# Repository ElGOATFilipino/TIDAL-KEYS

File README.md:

# TIDAL-KEYS

A 48 button BLE split keyboard with a design based on the geometry dash level "Tidal wave", features 20 SK6803MINI-E Leds total, and uses ZMK firmware. It is meant to be used as a regular keyboard, and the distance between each half is up to the user.

I made this because I wanted a split keyboard that felt unique to me! And since I love the game "geometry dash", I decided to base the design around one of its most popular community levels: Tidal wave. 

## Features per side:
- 24 white DSA keys
- 10 neopixel SK6803MINI-E LEDs (Light blue glow under the keys)
- BLE
- Hotswap keys
- 1000mAh 1S LiPo battery per side
- Battery sensing

## CAD Model: 

Both cases (left and right) are held together using 10 M2 screws and 10 heatset inserts per side. On both halves, 6 screws are used for the pcb and 4 of them for the top part of the case.
The case is made of only three separate pieces: the bottom, the top cover and the battery lid.

**Features of each component:**
- Bottom case: The bottom case has a hole, meant for the battery. This section also has a "tunnel" where the battery cables can easily connect to the PCB battery pads.
- Top lid: The top part features different types decorations from the level "Tidal wave", such as starfish, bubbles and its iconic title screen arrows.
- Battery lid: The battery lid is screwed to the case using 2 self-tapping M2 screws. The PCB sits over the bottom case using a 3x5x3mm spacer at the bottom and a 3x5x2mm spacer at the top per screw; sandwiching the PCB between them to prevent vertical wobble.

All case components made using Fusion 360.

## PCB:

Both the schematic and the PCB were designed in Kicad!

**Schematic:**

**PCB:** 
Backside of the PCB, since all components that belong to it are meant to be soldered on the back.
I used the regular cherry mx footprints, but it's meant to use MX2A. It also has a ground plane! That way there are less wires to connect (plus it looks cleaner)

**Wiring diagram (Battery connection):**
This part was made using Canva! 

## BOM:
To construct the full split keyboard, the following components are required:
- 1 PCB (file includes both halves)
- All six case components (Bottom, top, battery lid for each half)
- 2 Seeed studio XIAO nrf52840 modules
- 20 SK6803MINI-E Leds
- 48 Cherry MX2A switches (prefferably red)
- 48 1N5819 Diodes
- 20 0805 package 100nF capacitors
- 2 0805 package 300-ohm resistors
- 48 Kailh hotswap sockets
- 2 1000mAh 1S LiP Batteries
- 38 1u DSA keycaps (prefferably white)
- 1 1.25u DSA keycap (prefferably white)
- 2 1.75u DSA keycaps (prefferably white)
- 2 2u DSA keycaps (prefferably white)
- 1 2.25u DSA keycap (prefferably white)
- 2 2.75u DSA keycaps (prefferably white)
- 6 2u Clip-in Cherry stabilizers
- 20 16mm Pan head M2 screws (prefferably phillips-style socket)
- 4 4mm self tapping, pan head screws (prefferably phillips-style socket)
- 20 M2 OD3.5 heatset inserts
- 12 3x5x3mm rubber spacers (3mm inner diameter, 5mm outer diameter, 3mm thickness)
- 12 3x5x2mm rubber spacers (3mm inner diameter, 5mm outer diameter, 2mm thickness)

## How to enable BLE support

**Step 1**: Turn on both halves. This is done automatically when connecting the batteries.

**Step 2:** Press and hold `LSHIFT` + `G`. This activates a momentary layer that enables different BLE commands.
The following keys assume these functions when the momentary layer is activated:

- `1` → `BT_SEL 1` (Selects bluetooth layer 1)
- `2` → `BT_SEL 2` (Selects bluetooth layer 2)
- `3` → `BT_SEL 3` (Selects bluetooth layer 3)
- `4` → `BT_CLR` (Clears and purges all bluetooth connections)

**Step 3**: Select any of the bluetooth layer 1-3, the left keyboard will automatically connect with the right half, and broadcast a bluetooth pairing request to a host device. The user is free to release all keys after channel selection.

**Step 4**: In the host device's bluetooth tab, pair with "tidal_keys" and establish a connection with it.

**Step 5:** TIDAL-KEYS is all set and free to use!

## Additional notes: 

- TIDAL-KEYS does NOT have wired support! It is meant to be 100% BLE.
- Removing the battery to charge it is not necesary, since both keyboard halves contain a USB-C port just for that.
- In the `Firmware` folder, the files in `Compiled` are the .uf2 files meant to be flashed onto both nrf52840 modules (file name indicates which half), whereas `Tidal_keys_split_zmk` corresponds to the raw, uncompiled zmk firmware.

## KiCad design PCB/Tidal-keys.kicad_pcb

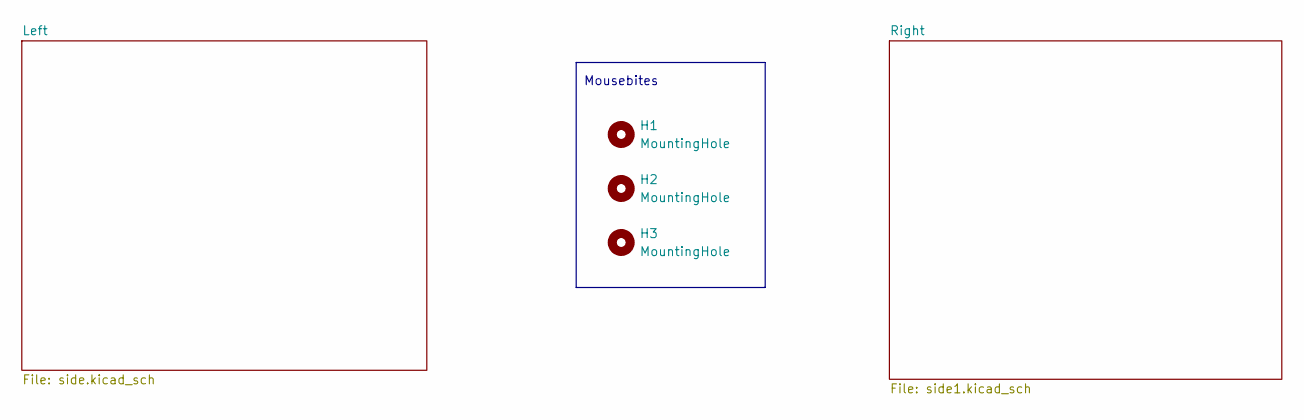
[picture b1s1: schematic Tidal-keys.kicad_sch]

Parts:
H1, H2, H3: MountingHole; mouse-bite-5mm-slot

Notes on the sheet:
Mousebites

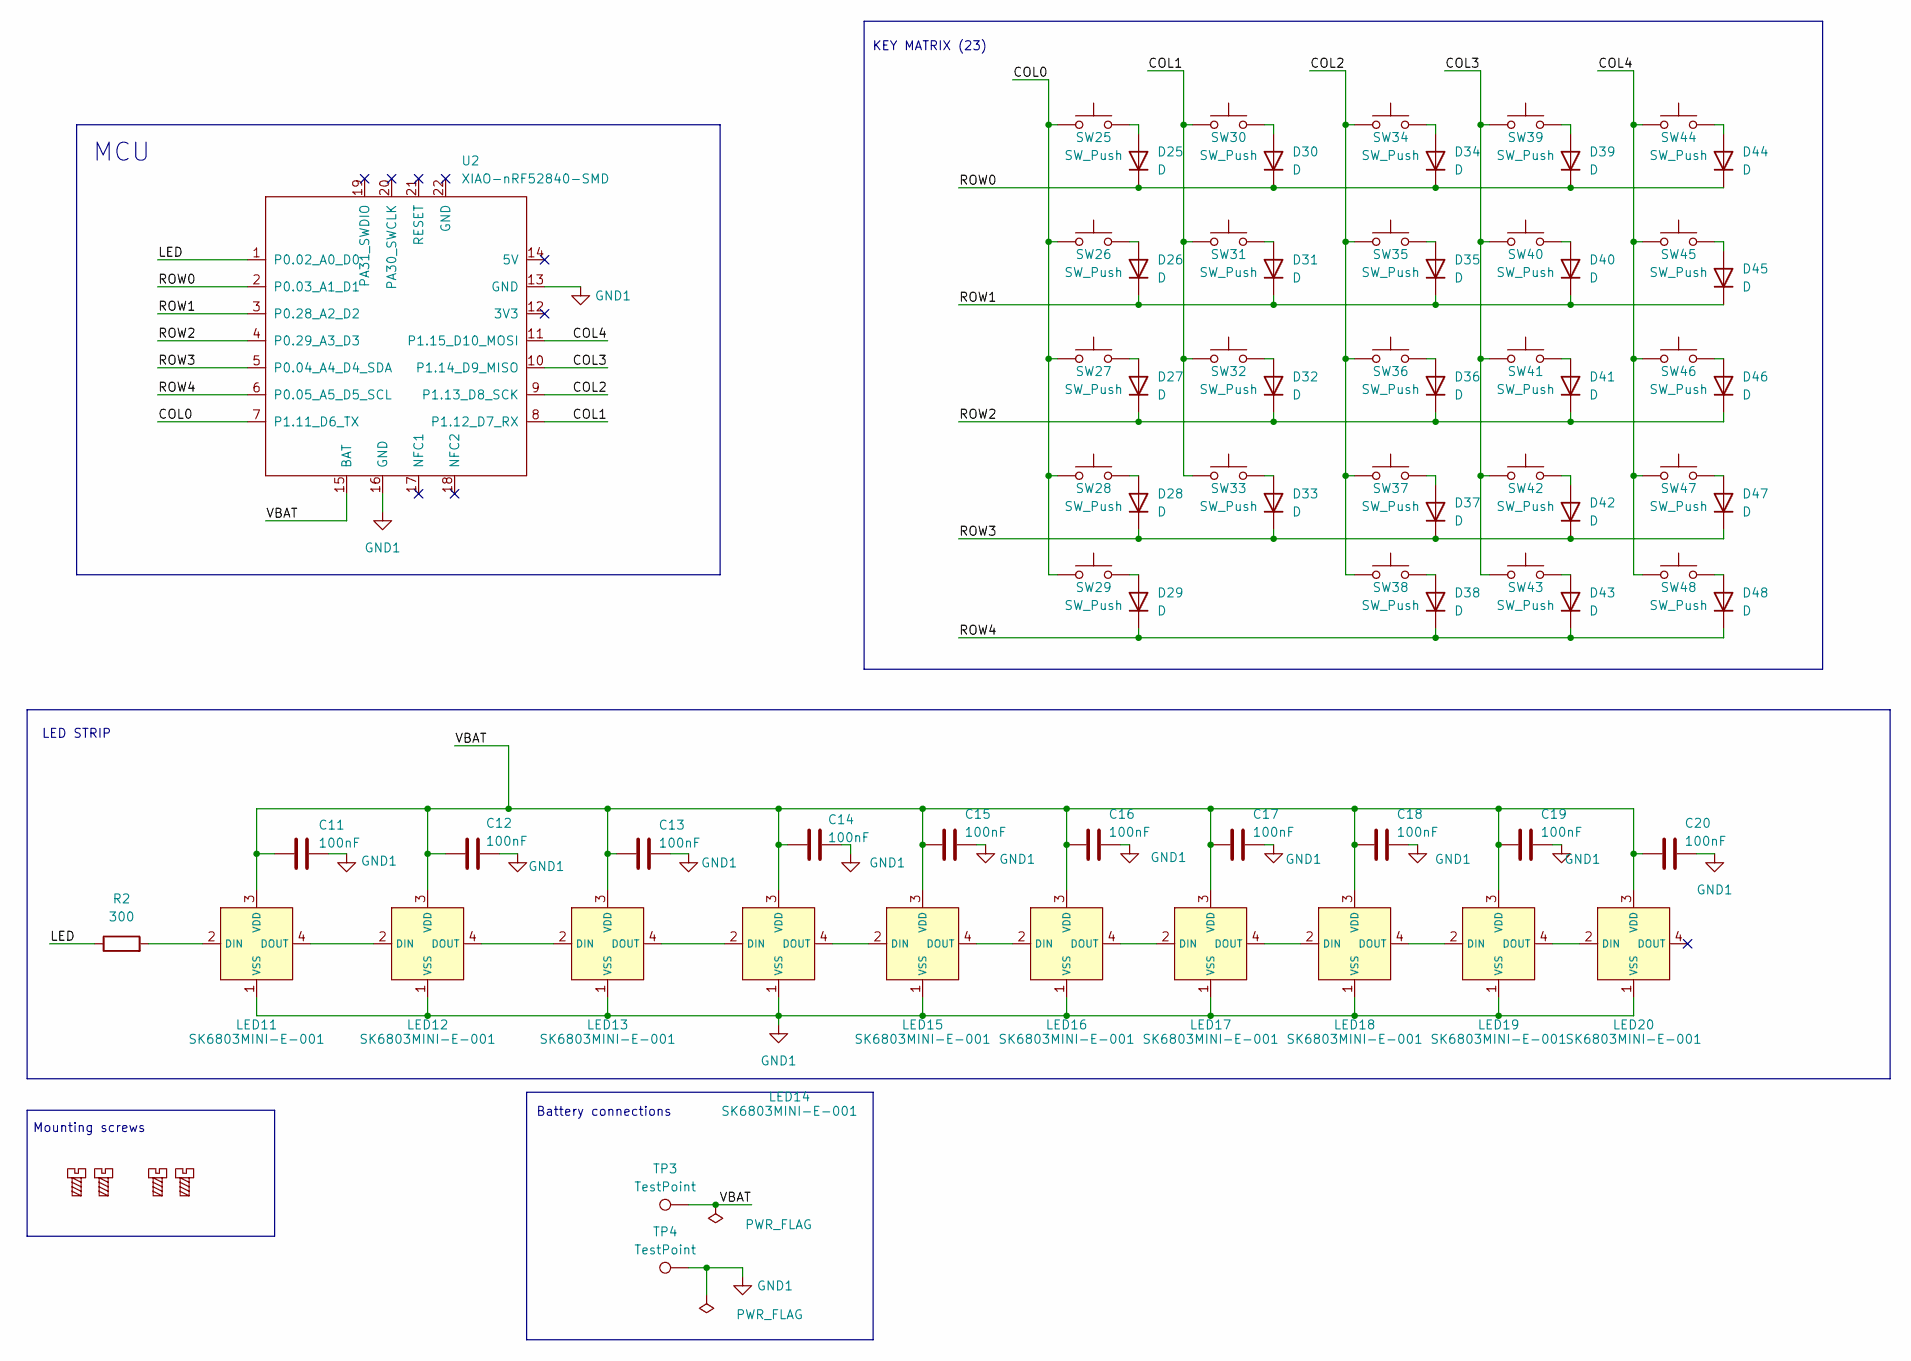
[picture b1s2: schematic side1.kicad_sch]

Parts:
C11, C12, C13, C14, C15, C16, C17, C18, C19, C20: 100nF; C_0805_2012Metric
D25, D26, D27, D28, D29, D30, D31, D32, D33, D34, D35, D36, D37, D38, D39, D40, D41, D42, D43, D44, D45, D46, D47, D48: D; D_SOD-123
H8, H9, H10, H11: MountingScrew; MountingHole_2.2mm_M2
LED11, LED12, LED13, LED14, LED15, LED16, LED17, LED18, LED19, LED20: SK6803MINI-E-001; LED_SK6812MINI-E_3.2x2.8mm_P1.5mm_ReverseMount; MPN SK6803MINI-E-001; LCSC Part C5242955
R2: 300; R_0805_2012Metric
SW25, SW26, SW27, SW28, SW29, SW30, SW31, SW32, SW33, SW34, SW35, SW36, SW37, SW38, SW39, SW40, SW41, SW42, SW43, SW44, SW45, SW46, SW47, SW48: SW_Push; SW_MX_HS_S_CPG151101S11_1u
TP3, TP4: TestPoint; TestPoint_Pad_D3.0mm
U2: XIAO-nRF52840-SMD; modified-XIAO-nRF52840-SMD

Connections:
/Right/COL0: SW25.1, SW26.1, SW27.1, SW28.1, SW29.1, U2.7 (P1.11_D6_TX)
/Right/COL1: SW30.1, SW31.1, SW32.1, SW33.1, U2.8 (P1.12_D7_RX)
/Right/COL2: SW34.1, SW35.1, SW36.1, SW37.1, SW38.1, U2.9 (P1.13_D8_SCK)
/Right/COL3: SW39.1, SW40.1, SW41.1, SW42.1, SW43.1, U2.10 (P1.14_D9_MISO)
/Right/COL4: SW44.1, SW45.1, SW46.1, SW47.1, SW48.1, U2.11 (P1.15_D10_MOSI)
/Right/LED: R2.1, U2.1 (P0.02_A0_D0)
/Right/ROW0: D25.1 (K), D30.1 (K), D34.1 (K), D39.1 (K), D44.1 (K), U2.2 (P0.03_A1_D1)
/Right/ROW1: D26.1 (K), D31.1 (K), D35.1 (K), D40.1 (K), D45.1 (K), U2.3 (P0.28_A2_D2)
/Right/ROW2: D27.1 (K), D32.1 (K), D36.1 (K), D41.1 (K), D46.1 (K), U2.4 (P0.29_A3_D3)
/Right/ROW3: D28.1 (K), D33.1 (K), D37.1 (K), D42.1 (K), D47.1 (K), U2.5 (P0.04_A4_D4_SDA)
/Right/ROW4: D29.1 (K), D38.1 (K), D43.1 (K), D48.1 (K), U2.6 (P0.05_A5_D5_SCL)
/Right/VBAT: C11.2, C12.2, C13.2, C14.2, C15.2, C16.2, C17.2, C18.2, C19.2, C20.2, LED11.3 (VDD), LED12.3 (VDD), LED13.3 (VDD), LED14.3 (VDD), LED15.3 (VDD), LED16.3 (VDD), LED17.3 (VDD), LED18.3 (VDD), LED19.3 (VDD), LED20.3 (VDD), TP3.1 (1_1), U2.15 (BAT)
GND1: C11.1, C12.1, C13.1, C14.1, C15.1, C16.1, C17.1, C18.1, C19.1, C20.1, LED11.1 (VSS), LED12.1 (VSS), LED13.1 (VSS), LED14.1 (VSS), LED15.1 (VSS), LED16.1 (VSS), LED17.1 (VSS), LED18.1 (VSS), LED19.1 (VSS), LED20.1 (VSS), TP4.1 (1_1), U2.13 (GND), U2.16 (GND)
unnamed: D25.2 (A), SW25.2
unnamed: D26.2 (A), SW26.2
unnamed: D27.2 (A), SW27.2
unnamed: D28.2 (A), SW28.2
unnamed: D29.2 (A), SW29.2
unnamed: D30.2 (A), SW30.2
unnamed: D31.2 (A), SW31.2
unnamed: D32.2 (A), SW32.2
unnamed: D33.2 (A), SW33.2
unnamed: D34.2 (A), SW34.2
unnamed: D35.2 (A), SW35.2
unnamed: D36.2 (A), SW36.2
unnamed: D37.2 (A), SW37.2
unnamed: D38.2 (A), SW38.2
unnamed: D39.2 (A), SW39.2
unnamed: D40.2 (A), SW40.2
unnamed: D41.2 (A), SW41.2
unnamed: D42.2 (A), SW42.2
unnamed: D43.2 (A), SW43.2
unnamed: D44.2 (A), SW44.2
unnamed: D45.2 (A), SW45.2
unnamed: D46.2 (A), SW46.2
unnamed: D47.2 (A), SW47.2
unnamed: D48.2 (A), SW48.2
unnamed: LED11.2 (DIN), R2.2
unnamed: LED11.4 (DOUT), LED12.2 (DIN)
unnamed: LED12.4 (DOUT), LED13.2 (DIN)
unnamed: LED13.4 (DOUT), LED14.2 (DIN)
unnamed: LED14.4 (DOUT), LED15.2 (DIN)
unnamed: LED15.4 (DOUT), LED16.2 (DIN)
unnamed: LED16.4 (DOUT), LED17.2 (DIN)
unnamed: LED17.4 (DOUT), LED18.2 (DIN)
unnamed: LED18.4 (DOUT), LED19.2 (DIN)
unnamed: LED19.4 (DOUT), LED20.2 (DIN)

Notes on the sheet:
MCU
Battery connections
LED STRIP
Mounting screws
KEY MATRIX (23)

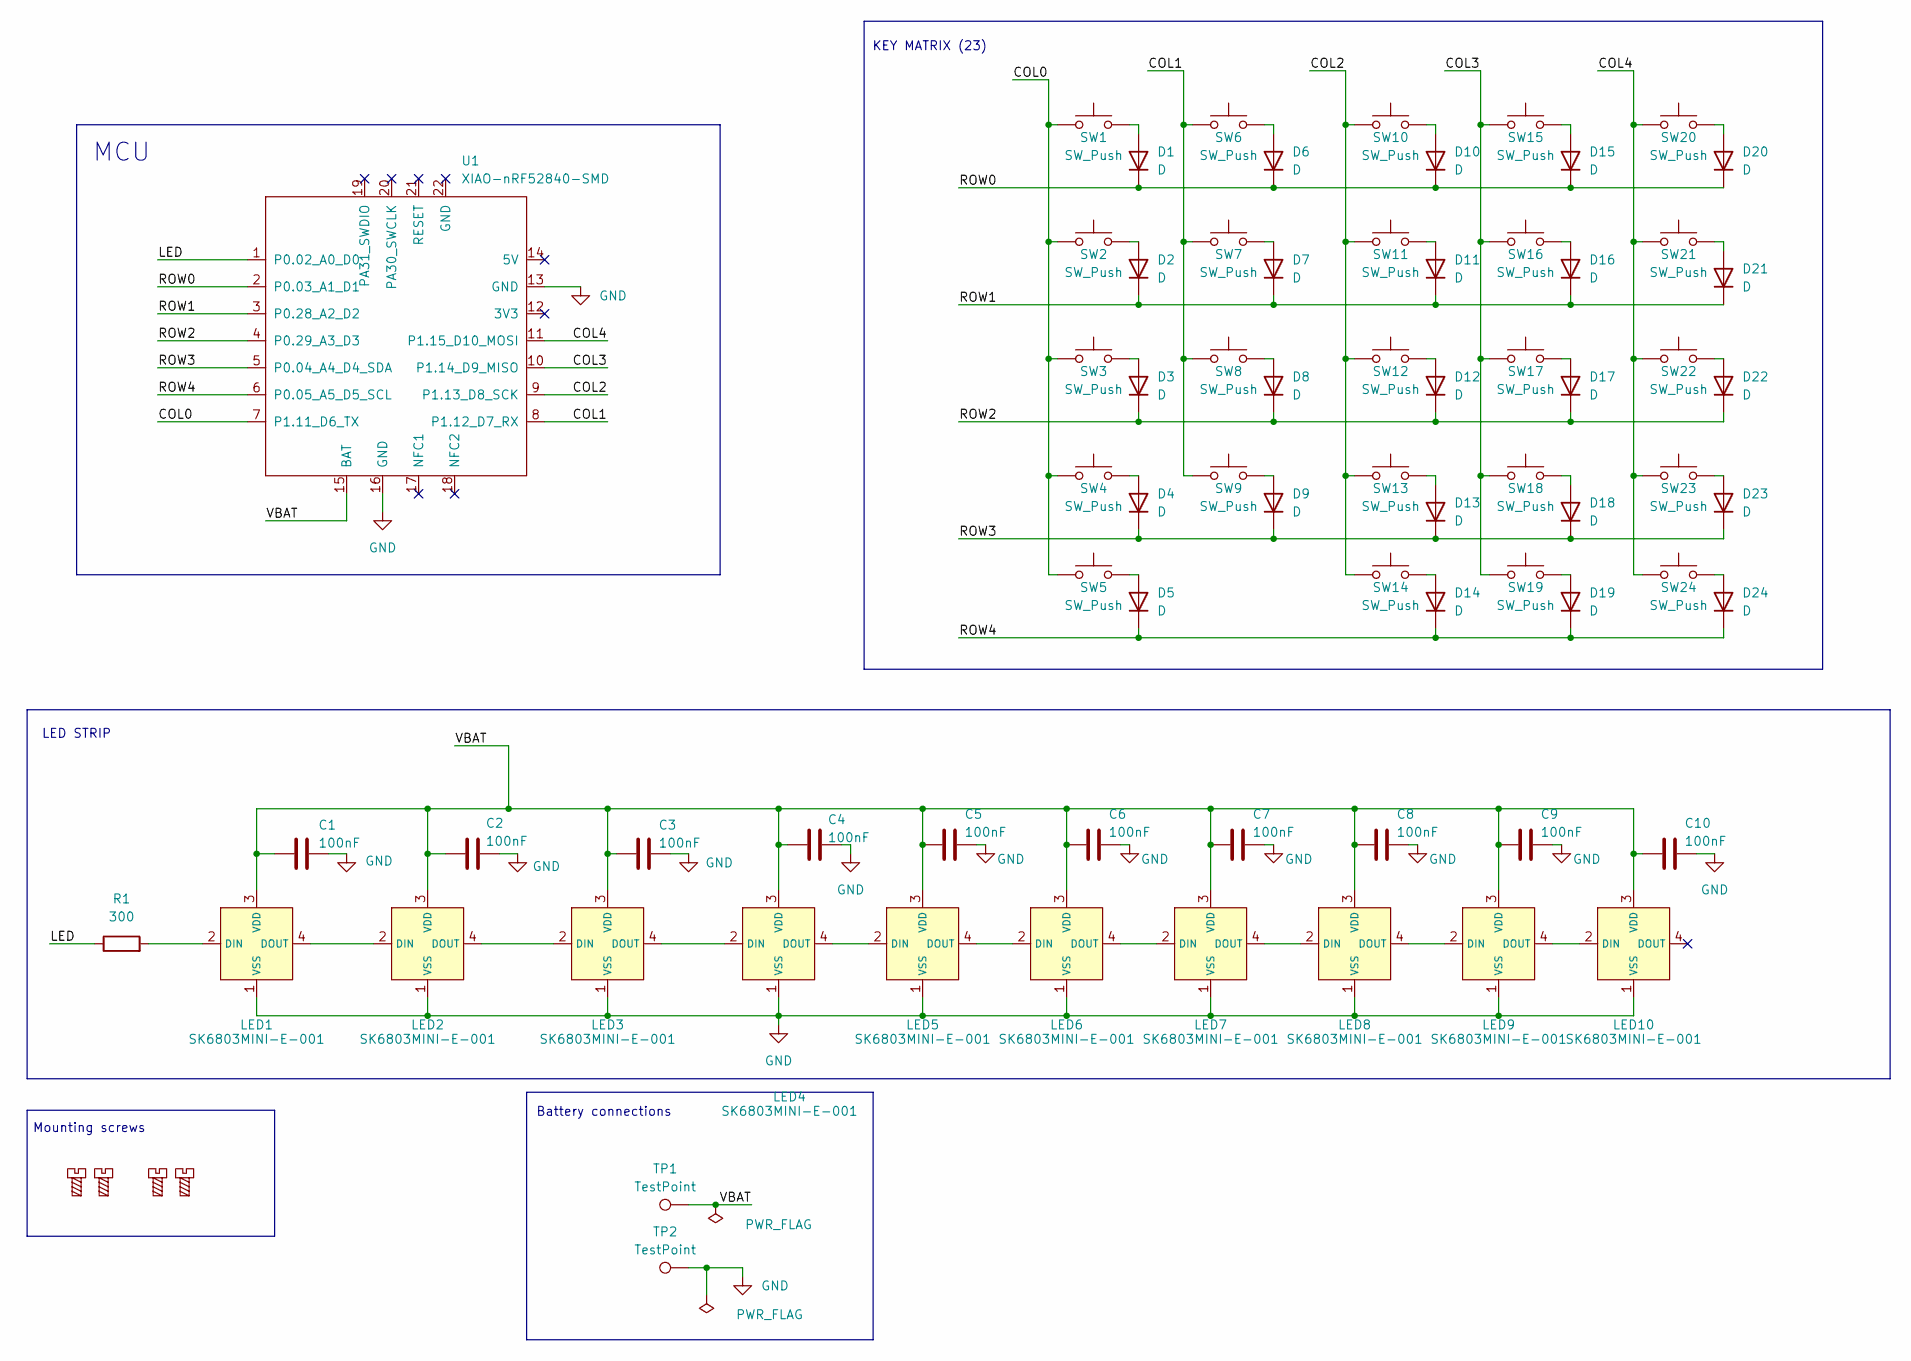
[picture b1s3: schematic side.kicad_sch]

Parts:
C1, C3, C4, C6, C7, C8, C9: 100nF; C_0805_2012Metric
C2, C5, C10: 100nF; C_0805_2012Metric; LCSC Part # C111492
D1, D2, D4, D5, D6, D7, D8, D10, D11, D12, D13, D14, D15, D16, D17, D18, D19, D20, D21, D22, D23, D24: D; D_SOD-123
D3, D9: D; D_SOD-123; LCSC Part # C963381
H4, H5, H6, H7: MountingScrew; MountingHole_2.2mm_M2
LED1, LED2, LED3, LED4, LED6, LED7, LED8, LED9, LED10: SK6803MINI-E-001; LED_SK6812MINI-E_3.2x2.8mm_P1.5mm_ReverseMount; MPN SK6803MINI-E-001; LCSC Part C5242955
LED5: SK6803MINI-E-001; LED_SK6812MINI-E_3.2x2.8mm_P1.5mm_ReverseMount; MPN SK6803MINI-E-001; LCSC Part # C5242955
R1: 300; R_0805_2012Metric; LCSC Part # C114529
SW1, SW2, SW3, SW4, SW5, SW6, SW7, SW8, SW9, SW10, SW11, SW12, SW13, SW14, SW15, SW16, SW17, SW18, SW19, SW20, SW21, SW22, SW23, SW24: SW_Push; SW_MX_HS_S_CPG151101S11_1u
TP1, TP2: TestPoint; TestPoint_Pad_D3.0mm
U1: XIAO-nRF52840-SMD; modified-XIAO-nRF52840-SMD

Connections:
/Left/COL0: SW1.1, SW2.1, SW3.1, SW4.1, SW5.1, U1.7 (P1.11_D6_TX)
/Left/COL1: SW6.1, SW7.1, SW8.1, SW9.1, U1.8 (P1.12_D7_RX)
/Left/COL2: SW10.1, SW11.1, SW12.1, SW13.1, SW14.1, U1.9 (P1.13_D8_SCK)
/Left/COL3: SW15.1, SW16.1, SW17.1, SW18.1, SW19.1, U1.10 (P1.14_D9_MISO)
/Left/COL4: SW20.1, SW21.1, SW22.1, SW23.1, SW24.1, U1.11 (P1.15_D10_MOSI)
/Left/LED: R1.1, U1.1 (P0.02_A0_D0)
/Left/ROW0: D1.1 (K), D6.1 (K), D10.1 (K), D15.1 (K), D20.1 (K), U1.2 (P0.03_A1_D1)
/Left/ROW1: D2.1 (K), D7.1 (K), D11.1 (K), D16.1 (K), D21.1 (K), U1.3 (P0.28_A2_D2)
/Left/ROW2: D3.1 (K), D8.1 (K), D12.1 (K), D17.1 (K), D22.1 (K), U1.4 (P0.29_A3_D3)
/Left/ROW3: D4.1 (K), D9.1 (K), D13.1 (K), D18.1 (K), D23.1 (K), U1.5 (P0.04_A4_D4_SDA)
/Left/ROW4: D5.1 (K), D14.1 (K), D19.1 (K), D24.1 (K), U1.6 (P0.05_A5_D5_SCL)
/Left/VBAT: C1.2, C2.2, C3.2, C4.2, C5.2, C6.2, C7.2, C8.2, C9.2, C10.2, LED1.3 (VDD), LED2.3 (VDD), LED3.3 (VDD), LED4.3 (VDD), LED5.3 (VDD), LED6.3 (VDD), LED7.3 (VDD), LED8.3 (VDD), LED9.3 (VDD), LED10.3 (VDD), TP1.1 (1_1), U1.15 (BAT)
GND: C1.1, C2.1, C3.1, C4.1, C5.1, C6.1, C7.1, C8.1, C9.1, C10.1, LED1.1 (VSS), LED2.1 (VSS), LED3.1 (VSS), LED4.1 (VSS), LED5.1 (VSS), LED6.1 (VSS), LED7.1 (VSS), LED8.1 (VSS), LED9.1 (VSS), LED10.1 (VSS), TP2.1 (1_1), U1.13 (GND), U1.16 (GND)
unnamed: D1.2 (A), SW1.2
unnamed: D2.2 (A), SW2.2
unnamed: D3.2 (A), SW3.2
unnamed: D4.2 (A), SW4.2
unnamed: D5.2 (A), SW5.2
unnamed: D6.2 (A), SW6.2
unnamed: D7.2 (A), SW7.2
unnamed: D8.2 (A), SW8.2
unnamed: D9.2 (A), SW9.2
unnamed: D10.2 (A), SW10.2
unnamed: D11.2 (A), SW11.2
unnamed: D12.2 (A), SW12.2
unnamed: D13.2 (A), SW13.2
unnamed: D14.2 (A), SW14.2
unnamed: D15.2 (A), SW15.2
unnamed: D16.2 (A), SW16.2
unnamed: D17.2 (A), SW17.2
unnamed: D18.2 (A), SW18.2
unnamed: D19.2 (A), SW19.2
unnamed: D20.2 (A), SW20.2
unnamed: D21.2 (A), SW21.2
unnamed: D22.2 (A), SW22.2
unnamed: D23.2 (A), SW23.2
unnamed: D24.2 (A), SW24.2
unnamed: LED1.2 (DIN), R1.2
unnamed: LED1.4 (DOUT), LED2.2 (DIN)
unnamed: LED2.4 (DOUT), LED3.2 (DIN)
unnamed: LED3.4 (DOUT), LED4.2 (DIN)
unnamed: LED4.4 (DOUT), LED5.2 (DIN)
unnamed: LED5.4 (DOUT), LED6.2 (DIN)
unnamed: LED6.4 (DOUT), LED7.2 (DIN)
unnamed: LED7.4 (DOUT), LED8.2 (DIN)
unnamed: LED8.4 (DOUT), LED9.2 (DIN)
unnamed: LED9.4 (DOUT), LED10.2 (DIN)

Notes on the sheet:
MCU
Battery connections
LED STRIP
Mounting screws
KEY MATRIX (23)

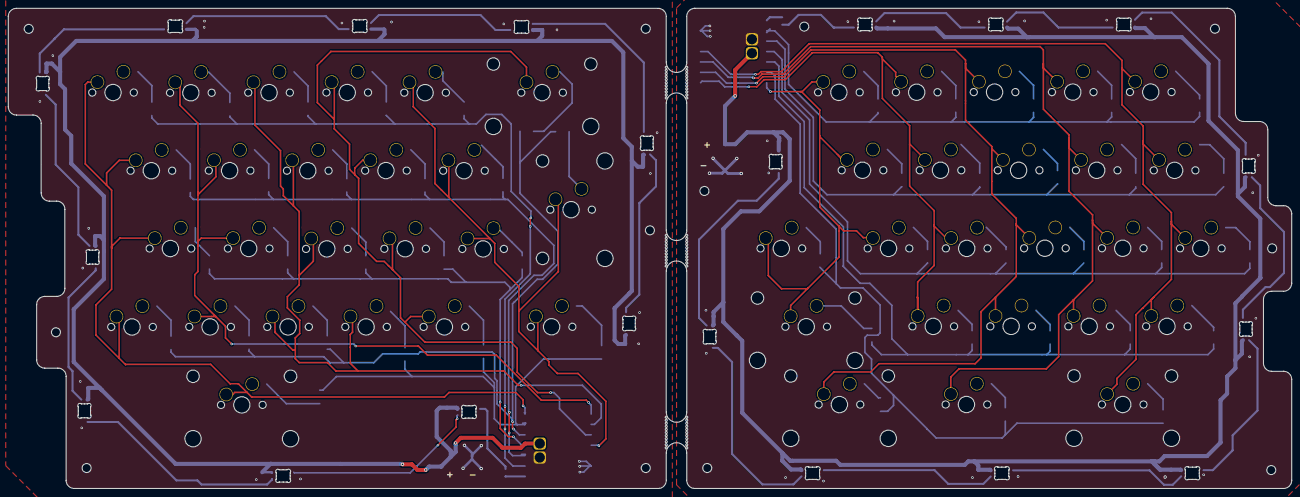
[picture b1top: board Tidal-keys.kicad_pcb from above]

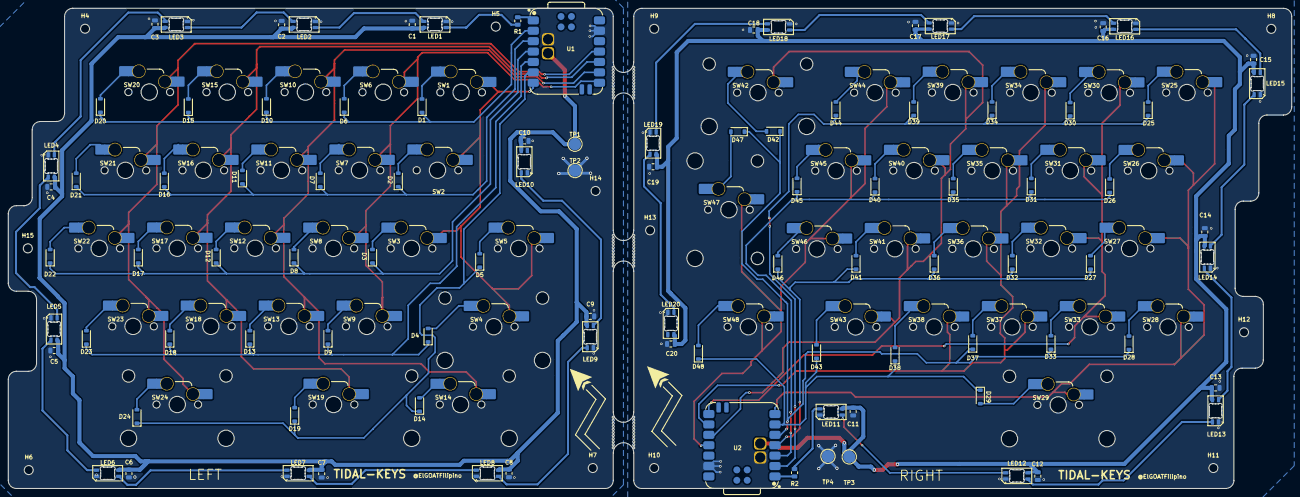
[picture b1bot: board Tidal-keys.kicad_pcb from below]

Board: 2 copper layers, 313.5 x 117.3 mm, 159 parts (159 on the bottom side), 94 nets.

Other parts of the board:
H12, H13, H14, H15: MountingScrew; MountingHole_2.2mm_M2

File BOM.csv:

Item Name,Qty (Actual used),Qty (Bundle amount),Value,Price (total),Shipping fee?,Footprint,Item link,Additional notes
PCB,1,5,PCB,$21.70,No,N/A,https://github.com/ElGOATFilipino/TIDAL-KEYS/blob/main/Produ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,
"Capacitors, 100nf, 0805, ±5%, X7R",20,20,100nF,$0.21,No,Capacitor_SMD:C_0805_2012Metric,https://jlcpcb.com/partdetail/YAGEO-CC0805JRX7R9BB104/C111492,
"Diodes, 1N5819, 13A, 40V",48,48,D,$0.48,No,Diode_SMD:D_SOD-123,https://jlcpcb.com/partdetail/JSMSEMI-1N5819W/C963381,
"LEDs, neopixel, 3mA",20,20,SK6803MINI-E-001,$1.71,No,LED_SMD:LED_SK6812MINI-E_3.2x2.8mm_P1.5mm_ReverseMount,https://jlcpcb.com/partdetail/5951765-SK6803MINI_E001/C5242955,
"Resistors, 300Ω, 150V, ±1%, 0805",2,2,300,$0.01,No,Resistor_SMD:R_0805_2012Metric,https://jlcpcb.com/partdetail/YAGEO-RC0805FR07300RL/C114529,
"Cherry MX2A switches, Red,  RGB, 5 pins, 70 pcs ",48,70,SW_Push,$29.63,No,Keyboard_stuff:SW_MX_HS_S_CPG151101S11_1u,https://es.aliexpress.com/item/1005008402977550.html?spm=a2g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,"Even though the keyboard only uses 50 pcs, I couldnt find any better deal, since buying separate combos still costs more than the 29.63 dollars"
Kailh Hotswap sockets,48,50,SW_Push,$9.64,No,Keyboard_stuff:SW_MX_HS_S_CPG151101S11_1u,https://es.aliexpress.com/item/1005007639688349.html?spm=a2g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,
"Seeed studio XIAO nrf52840 module, BLE",2,2,XIAO-nRF52840-SMD,$21.96,Yes,Kicad_care_package:modified-XIAO-nRF52840-SMD,https://es.aliexpress.com/item/1005006988954136.html?spm=a2g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,Shipping price=$6.61
Case components (all 3d printed),1,1,Case components,$34,No,N/A,https://github.com/ElGOATFilipino/TIDAL-KEYS/tree/main/CAD,Shipping price is included in the total price
"LiPo Batteries, 1S, 3.7V, 1000mAh, 503450",2,2,Batteries,$6.87,No,N/A,https://es.aliexpress.com/item/1005013103110427.html?spm=a2g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,
"Keycaps, Dsa, 1u, white",38,50,1u,$5.41,No,N/A,https://es.aliexpress.com/item/1005010720096151.html?src=goo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,
"Keycaps, DSA, 1.25u, white",1,10,1.25u,$1.15,No,N/A,https://es.aliexpress.com/item/1005008827506189.html?src=goo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,
"Keycaps, DSA, 1.75u, white",2,2,1.75u,$7.96,No,N/A,https://es.aliexpress.com/item/4001241957677.html?gatewayAda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,
"Keycaps,  DSA, 2u, white",2,10,2u,$4.27,No,N/A,https://es.aliexpress.com/item/1005009085514680.html?spm=a2g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,
"Keycaps, DSA, 2.25u, white",1,3,2.25u,$8.42,No,N/A,https://es.aliexpress.com/item/4001241957677.html?src=google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,
"Keycaps, DSA, 2.75u, white",2,2,2.75u,$8.13,No,N/A,https://es.aliexpress.com/item/4001241957677.html?src=google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,
"Keycap Stabilizer, 2u, Clip in, Cherry",6,6,Stabilizers,$7.20,Yes,STAB_MX_2u & STAB_MX_ISO (see notes),https://es.aliexpress.com/item/32864774665.html?gatewayAdapt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,Shipping fee = $5.54
"Screws, M2, 16mm, Pan Head, Phillips",20,50,Screws,$1.78,No,MountingHole_2.2mm_M2,https://es.aliexpress.com/item/1005007182988353.html?spm=a2g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,
"Screws, M2, Self tapping, Pan Head, 4mm length",4,50,Screws,$1.09,No,N/A,https://es.aliexpress.com/item/1005007288501133.html?spm=a2g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,
"Heatset Inserts, Brass, M2, OD3.5mm, L4",20,50,Heatset inserts,$1.09,No,N/A,https://es.aliexpress.com/item/1005008666672949.html?src=goo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,This aliexpress link was actually listed previously on the blueprint ysws website.
"Rubber mounts, 3x5x3mm",12,50,Spacers,$2.32,Yes,N/A,https://es.aliexpress.com/item/1005011938076290.html?spm=a2g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,Shipping fee = $2.95
"Rubber mounts, 3x5x2mm",12,50,Spacers,$1.90,Yes,N/A,https://es.aliexpress.com/item/1005011938076290.html?spm=a2g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,Shipping fee = $2.95
Shipping fee total (Aliexpress),N/A,N/A,Delivery,$18.05,N/A,N/A,"All items with ""yes"" listed in ""shipping fee?""",
Total,N/A,N/A,Total price,"$194,98",N/A,N/A,N/A,
